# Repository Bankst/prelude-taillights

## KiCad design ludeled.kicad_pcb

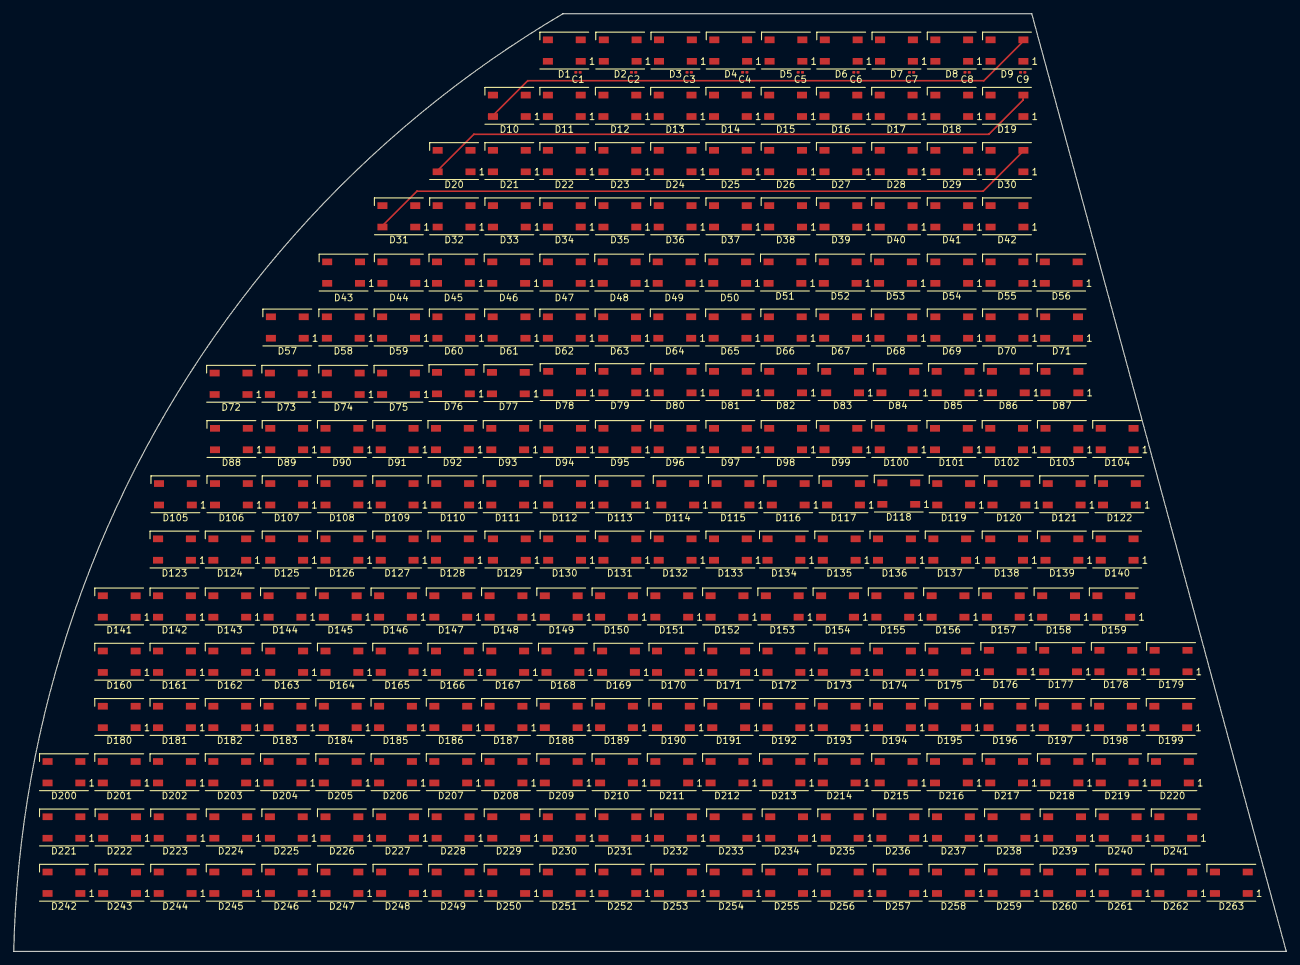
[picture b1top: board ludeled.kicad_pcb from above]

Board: 2 copper layers, 190.0 x 140.0 mm, 273 parts (1 on the bottom side), 224 nets.

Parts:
C1, C2, C3, C4, C5, C6, C7, C8, C9: 100nF; C_0201_0603Metric
D1, D2, D3, D4, D5, D6, D7, D8, D9, D10, D11, D12, D13, D14, D15, D16, D17, D18, D19, D20, D21, D22, D23, D24, D25, D26, D27, D28, D29, D30, D31, D32, D33, D34, D35, D36, D37, D38, D39, D40, D41, D42, D43, D44, D45, D46, D47, D48, D49, D50, D51, D52, D53, D54, D55, D56, D57, D58, D59, D60, D61, D62, D63, D64, D65, D66, D67, D68, D69, D70, D71, D72, D73, D74, D75, D76, D77, D78, D79, D80, D81, D82, D83, D84, D85, D86, D87, D88, D89, D90, D91, D92, D93, D94, D95, D96, D97, D98, D99, D100, D101, D102, D103, D104, D105, D106, D107, D108, D109, D110, D111, D112, D113, D114, D115, D116, D117, D118, D119, D120, D121, D122, D123, D124, D125, D126, D127, D128, D129, D130, D131, D132, D133, D134, D135, D136, D137, D138, D139, D140, D141, D142, D143, D144, D145, D146, D147, D148, D149, D150, D151, D152, D153, D154, D155, D156, D157, D158, D159, D160, D161, D162, D163, D164, D165, D166, D167, D168, D169, D170, D171, D172, D173, D174, D175, D176, D177, D178, D179, D180, D181, D182, D183, D184, D185, D186, D187, D188, D189, D190, D191, D192, D193, D194, D195, D196, D197, D198, D199, D200, D201, D202, D203, D204, D205, D206, D207, D208, D209, D210, D211, D212, D213, D214, D215, D216, D217, D218, D219, D220, D221, D222, D223, D224, D225, D226, D227, D228, D229, D230, D231, D232, D233, D234, D235, D236, D237, D238, D239, D240, D241, D242, D243, D244, D245, D246, D247, D248, D249, D250, D251, D252, D253, D254, D255, D256, D257, D258, D259, D260, D261, D262, D263: WS2812B; LED_WS2812B_PLCC4_5.0x5.0mm_P3.2mm
U1: ESP32-WROOM-32E

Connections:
+5V: C1.1, C2.1, C3.1, C4.1, C5.1, C6.1, C7.1, C8.1, C9.1, D1.1 (VDD), D2.1 (VDD), D3.1 (VDD), D4.1 (VDD), D5.1 (VDD), D6.1 (VDD), D7.1 (VDD), D8.1 (VDD), D9.1 (VDD), D10.1 (VDD), D11.1 (VDD), D12.1 (VDD), D13.1 (VDD), D14.1 (VDD), D15.1 (VDD), D16.1 (VDD), D17.1 (VDD), D18.1 (VDD), D19.1 (VDD), D20.1 (VDD), D21.1 (VDD), D22.1 (VDD), D23.1 (VDD), D24.1 (VDD), D25.1 (VDD), D26.1 (VDD), D27.1 (VDD), D28.1 (VDD), D29.1 (VDD), D30.1 (VDD), D31.1 (VDD), D32.1 (VDD), D33.1 (VDD), D34.1 (VDD), D35.1 (VDD), D36.1 (VDD), D37.1 (VDD), D38.1 (VDD), D39.1 (VDD), D40.1 (VDD), D41.1 (VDD), D42.1 (VDD), D43.1 (VDD), D44.1 (VDD), D45.1 (VDD), D46.1 (VDD), D47.1 (VDD), D48.1 (VDD), D49.1 (VDD), D50.1 (VDD), D51.1 (VDD), D52.1 (VDD), D53.1 (VDD), D54.1 (VDD), D55.1 (VDD), D56.1 (VDD), D57.1 (VDD), D58.1 (VDD), D59.1 (VDD), D60.1 (VDD), D61.1 (VDD), D62.1 (VDD), D63.1 (VDD), D64.1 (VDD), D65.1 (VDD), D66.1 (VDD), D67.1 (VDD), D68.1 (VDD), D69.1 (VDD), D70.1 (VDD), D71.1 (VDD), D72.1 (VDD), D73.1 (VDD), D74.1 (VDD), D75.1 (VDD), D76.1 (VDD), D77.1 (VDD), D78.1 (VDD), D79.1 (VDD), D80.1 (VDD), D81.1 (VDD), D82.1 (VDD), D83.1 (VDD), D84.1 (VDD), D85.1 (VDD), D86.1 (VDD), D87.1 (VDD), D88.1 (VDD), D89.1 (VDD), D90.1 (VDD), D91.1 (VDD), D92.1 (VDD), D93.1 (VDD), D94.1 (VDD), D95.1 (VDD), D96.1 (VDD), D97.1 (VDD), D98.1 (VDD), D99.1 (VDD), D100.1 (VDD), D101.1 (VDD), D102.1 (VDD), D103.1 (VDD), D104.1 (VDD), D105.1 (VDD), D106.1 (VDD), D107.1 (VDD), D108.1 (VDD), D109.1 (VDD), D110.1 (VDD), D111.1 (VDD), D112.1 (VDD), D113.1 (VDD), D114.1 (VDD), D115.1 (VDD), D116.1 (VDD), D117.1 (VDD), D118.1 (VDD), D119.1 (VDD), D120.1 (VDD), D121.1 (VDD), D122.1 (VDD), D123.1 (VDD), D124.1 (VDD), D125.1 (VDD), D126.1 (VDD), D127.1 (VDD), D128.1 (VDD), D129.1 (VDD), D130.1 (VDD), D131.1 (VDD), D132.1 (VDD), D133.1 (VDD), D134.1 (VDD), D135.1 (VDD), D136.1 (VDD), D137.1 (VDD), D138.1 (VDD), D139.1 (VDD), D140.1 (VDD), D141.1 (VDD), D142.1 (VDD), D143.1 (VDD), D144.1 (VDD), D145.1 (VDD), D146.1 (VDD), D147.1 (VDD), D148.1 (VDD), D149.1 (VDD), D150.1 (VDD), D151.1 (VDD), D152.1 (VDD), D153.1 (VDD), D154.1 (VDD), D155.1 (VDD), D156.1 (VDD), D157.1 (VDD), D158.1 (VDD), D159.1 (VDD), D160.1 (VDD), D161.1 (VDD), D162.1 (VDD), D163.1 (VDD), D164.1 (VDD), D165.1 (VDD), D166.1 (VDD), D167.1 (VDD), D168.1 (VDD), D169.1 (VDD), D170.1 (VDD), D171.1 (VDD), D172.1 (VDD), D173.1 (VDD), D174.1 (VDD), D175.1 (VDD), D176.1 (VDD), D177.1 (VDD), D178.1 (VDD), D179.1 (VDD), D180.1 (VDD), D181.1 (VDD), D182.1 (VDD), D183.1 (VDD), D184.1 (VDD), D185.1 (VDD), D186.1 (VDD), D187.1 (VDD), D188.1 (VDD), D189.1 (VDD), D190.1 (VDD), D191.1 (VDD), D192.1 (VDD), D193.1 (VDD), D194.1 (VDD), D195.1 (VDD), D196.1 (VDD), D197.1 (VDD), D198.1 (VDD), D199.1 (VDD), D200.1 (VDD), D201.1 (VDD), D202.1 (VDD), D203.1 (VDD), D204.1 (VDD), D205.1 (VDD), D206.1 (VDD), D207.1 (VDD), D208.1 (VDD), D209.1 (VDD), D210.1 (VDD), D211.1 (VDD), D212.1 (VDD), D213.1 (VDD), D214.1 (VDD), D215.1 (VDD), D216.1 (VDD), D217.1 (VDD), D218.1 (VDD), D219.1 (VDD), D220.1 (VDD), D221.1 (VDD), D222.1 (VDD), D223.1 (VDD), D224.1 (VDD), D225.1 (VDD), D226.1 (VDD), D227.1 (VDD), D228.1 (VDD), D229.1 (VDD), D230.1 (VDD), D231.1 (VDD), D232.1 (VDD), D233.1 (VDD), D234.1 (VDD), D235.1 (VDD), D236.1 (VDD), D237.1 (VDD), D238.1 (VDD), D239.1 (VDD), D240.1 (VDD), D241.1 (VDD), D242.1 (VDD), D243.1 (VDD), D244.1 (VDD), D245.1 (VDD), D246.1 (VDD), D247.1 (VDD), D248.1 (VDD), D249.1 (VDD), D250.1 (VDD), D251.1 (VDD), D252.1 (VDD), D253.1 (VDD), D254.1 (VDD), D255.1 (VDD), D256.1 (VDD), D257.1 (VDD), D258.1 (VDD), D259.1 (VDD), D260.1 (VDD), D261.1 (VDD), D262.1 (VDD), D263.1 (VDD)
/FrontLeds/LED_LOWER_DIN: D1.4 (DIN), U1.29
GND: C1.2, C2.2, C3.2, C4.2, C5.2, C6.2, C7.2, C8.2, C9.2, D1.3 (VSS), D2.3 (VSS), D3.3 (VSS), D4.3 (VSS), D5.3 (VSS), D6.3 (VSS), D7.3 (VSS), D8.3 (VSS), D9.3 (VSS), D10.3 (VSS), D11.3 (VSS), D12.3 (VSS), D13.3 (VSS), D14.3 (VSS), D15.3 (VSS), D16.3 (VSS), D17.3 (VSS), D18.3 (VSS), D19.3 (VSS), D20.3 (VSS), D21.3 (VSS), D22.3 (VSS), D23.3 (VSS), D24.3 (VSS), D25.3 (VSS), D26.3 (VSS), D27.3 (VSS), D28.3 (VSS), D29.3 (VSS), D30.3 (VSS), D31.3 (VSS), D32.3 (VSS), D33.3 (VSS), D34.3 (VSS), D35.3 (VSS), D36.3 (VSS), D37.3 (VSS), D38.3 (VSS), D39.3 (VSS), D40.3 (VSS), D41.3 (VSS), D42.3 (VSS), D43.3 (VSS), D44.3 (VSS), D45.3 (VSS), D46.3 (VSS), D47.3 (VSS), D48.3 (VSS), D49.3 (VSS), D50.3 (VSS), D51.3 (VSS), D52.3 (VSS), D53.3 (VSS), D54.3 (VSS), D55.3 (VSS), D56.3 (VSS), D57.3 (VSS), D58.3 (VSS), D59.3 (VSS), D60.3 (VSS), D61.3 (VSS), D62.3 (VSS), D63.3 (VSS), D64.3 (VSS), D65.3 (VSS), D66.3 (VSS), D67.3 (VSS), D68.3 (VSS), D69.3 (VSS), D70.3 (VSS), D71.3 (VSS), D72.3 (VSS), D73.3 (VSS), D74.3 (VSS), D75.3 (VSS), D76.3 (VSS), D77.3 (VSS), D78.3 (VSS), D79.3 (VSS), D80.3 (VSS), D81.3 (VSS), D82.3 (VSS), D83.3 (VSS), D84.3 (VSS), D85.3 (VSS), D86.3 (VSS), D87.3 (VSS), D88.3 (VSS), D89.3 (VSS), D90.3 (VSS), D91.3 (VSS), D92.3 (VSS), D93.3 (VSS), D94.3 (VSS), D95.3 (VSS), D96.3 (VSS), D97.3 (VSS), D98.3 (VSS), D99.3 (VSS), D100.3 (VSS), D101.3 (VSS), D102.3 (VSS), D103.3 (VSS), D104.3 (VSS), D105.3 (VSS), D106.3 (VSS), D107.3 (VSS), D108.3 (VSS), D109.3 (VSS), D110.3 (VSS), D111.3 (VSS), D112.3 (VSS), D113.3 (VSS), D114.3 (VSS), D115.3 (VSS), D116.3 (VSS), D117.3 (VSS), D118.3 (VSS), D119.3 (VSS), D120.3 (VSS), D121.3 (VSS), D122.3 (VSS), D123.3 (VSS), D124.3 (VSS), D125.3 (VSS), D126.3 (VSS), D127.3 (VSS), D128.3 (VSS), D129.3 (VSS), D130.3 (VSS), D131.3 (VSS), D132.3 (VSS), D133.3 (VSS), D134.3 (VSS), D135.3 (VSS), D136.3 (VSS), D137.3 (VSS), D138.3 (VSS), D139.3 (VSS), D140.3 (VSS), D141.3 (VSS), D142.3 (VSS), D143.3 (VSS), D144.3 (VSS), D145.3 (VSS), D146.3 (VSS), D147.3 (VSS), D148.3 (VSS), D149.3 (VSS), D150.3 (VSS), D151.3 (VSS), D152.3 (VSS), D153.3 (VSS), D154.3 (VSS), D155.3 (VSS), D156.3 (VSS), D157.3 (VSS), D158.3 (VSS), D159.3 (VSS), D160.3 (VSS), D161.3 (VSS), D162.3 (VSS), D163.3 (VSS), D164.3 (VSS), D165.3 (VSS), D166.3 (VSS), D167.3 (VSS), D168.3 (VSS), D169.3 (VSS), D170.3 (VSS), D171.3 (VSS), D172.3 (VSS), D173.3 (VSS), D174.3 (VSS), D175.3 (VSS), D176.3 (VSS), D177.3 (VSS), D178.3 (VSS), D179.3 (VSS), D180.3 (VSS), D181.3 (VSS), D182.3 (VSS), D183.3 (VSS), D184.3 (VSS), D185.3 (VSS), D186.3 (VSS), D187.3 (VSS), D188.3 (VSS), D189.3 (VSS), D190.3 (VSS), D191.3 (VSS), D192.3 (VSS), D193.3 (VSS), D194.3 (VSS), D195.3 (VSS), D196.3 (VSS), D197.3 (VSS), D198.3 (VSS), D199.3 (VSS), D200.3 (VSS), D201.3 (VSS), D202.3 (VSS), D203.3 (VSS), D204.3 (VSS), D205.3 (VSS), D206.3 (VSS), D207.3 (VSS), D208.3 (VSS), D209.3 (VSS), D210.3 (VSS), D211.3 (VSS), D212.3 (VSS), D213.3 (VSS), D214.3 (VSS), D215.3 (VSS), D216.3 (VSS), D217.3 (VSS), D218.3 (VSS), D219.3 (VSS), D220.3 (VSS), D221.3 (VSS), D222.3 (VSS), D223.3 (VSS), D224.3 (VSS), D225.3 (VSS), D226.3 (VSS), D227.3 (VSS), D228.3 (VSS), D229.3 (VSS), D230.3 (VSS), D231.3 (VSS), D232.3 (VSS), D233.3 (VSS), D234.3 (VSS), D235.3 (VSS), D236.3 (VSS), D237.3 (VSS), D238.3 (VSS), D239.3 (VSS), D240.3 (VSS), D241.3 (VSS), D242.3 (VSS), D243.3 (VSS), D244.3 (VSS), D245.3 (VSS), D246.3 (VSS), D247.3 (VSS), D248.3 (VSS), D249.3 (VSS), D250.3 (VSS), D251.3 (VSS), D252.3 (VSS), D253.3 (VSS), D254.3 (VSS), D255.3 (VSS), D256.3 (VSS), D257.3 (VSS), D258.3 (VSS), D259.3 (VSS), D260.3 (VSS), D261.3 (VSS), D262.3 (VSS), D263.3 (VSS), U1.1, U1.15, U1.38
unnamed: D1.2 (DOUT), D2.4 (DIN)
unnamed: D2.2 (DOUT), D3.4 (DIN)
unnamed: D3.2 (DOUT), D4.4 (DIN)
unnamed: D4.2 (DOUT), D5.4 (DIN)
unnamed: D5.2 (DOUT), D6.4 (DIN)
unnamed: D6.2 (DOUT), D7.4 (DIN)
unnamed: D7.2 (DOUT), D8.4 (DIN)
unnamed: D8.2 (DOUT), D9.4 (DIN)
unnamed: D10.2 (DOUT), D11.4 (DIN)
unnamed: D9.2 (DOUT), D10.4 (DIN)
unnamed: D11.2 (DOUT), D12.4 (DIN)
unnamed: D12.2 (DOUT), D13.4 (DIN)
unnamed: D13.2 (DOUT), D14.4 (DIN)
unnamed: D14.2 (DOUT), D15.4 (DIN)
unnamed: D15.2 (DOUT), D16.4 (DIN)
unnamed: D16.2 (DOUT), D17.4 (DIN)
unnamed: D17.2 (DOUT), D18.4 (DIN)
unnamed: D18.2 (DOUT), D19.4 (DIN)
unnamed: D19.2 (DOUT), D20.4 (DIN)
unnamed: D20.2 (DOUT), D21.4 (DIN)
unnamed: D21.2 (DOUT), D22.4 (DIN)
unnamed: D22.2 (DOUT), D23.4 (DIN)
unnamed: D23.2 (DOUT), D24.4 (DIN)
unnamed: D24.2 (DOUT), D25.4 (DIN)
unnamed: D25.2 (DOUT), D26.4 (DIN)
unnamed: D26.2 (DOUT), D27.4 (DIN)
unnamed: D27.2 (DOUT), D28.4 (DIN)
unnamed: D28.2 (DOUT), D29.4 (DIN)
unnamed: D29.2 (DOUT), D30.4 (DIN)
unnamed: D30.2 (DOUT), D31.4 (DIN)
unnamed: D31.2 (DOUT), D32.4 (DIN)
unnamed: D32.2 (DOUT), D33.4 (DIN)
unnamed: D33.2 (DOUT), D34.4 (DIN)
unnamed: D34.2 (DOUT), D35.4 (DIN)
unnamed: D35.2 (DOUT), D36.4 (DIN)
unnamed: D36.2 (DOUT), D37.4 (DIN)
unnamed: D37.2 (DOUT), D38.4 (DIN)
unnamed: D38.2 (DOUT), D39.4 (DIN)
unnamed: D39.2 (DOUT), D40.4 (DIN)
unnamed: D40.2 (DOUT), D41.4 (DIN)
unnamed: D41.2 (DOUT), D42.4 (DIN)
unnamed: D42.2 (DOUT), D43.4 (DIN)
unnamed: D43.2 (DOUT), D44.4 (DIN)
unnamed: D44.2 (DOUT), D45.4 (DIN)
unnamed: D45.2 (DOUT), D46.4 (DIN)
unnamed: D46.2 (DOUT), D47.4 (DIN)
unnamed: D47.2 (DOUT), D48.4 (DIN)
unnamed: D48.2 (DOUT), D49.4 (DIN)
unnamed: D49.2 (DOUT), D50.4 (DIN)
unnamed: D50.2 (DOUT), D51.4 (DIN)
unnamed: D51.2 (DOUT), D52.4 (DIN)
unnamed: D52.2 (DOUT), D53.4 (DIN)
unnamed: D53.2 (DOUT), D54.4 (DIN)
unnamed: D54.2 (DOUT), D55.4 (DIN)
unnamed: D55.2 (DOUT), D56.4 (DIN)
unnamed: D56.2 (DOUT), D57.4 (DIN)
unnamed: D57.2 (DOUT), D58.4 (DIN)
unnamed: D58.2 (DOUT), D59.4 (DIN)
unnamed: D59.2 (DOUT), D60.4 (DIN)
unnamed: D60.2 (DOUT), D61.4 (DIN)
unnamed: D61.2 (DOUT), D62.4 (DIN)
unnamed: D62.2 (DOUT), D63.4 (DIN)
unnamed: D63.2 (DOUT), D64.4 (DIN)
unnamed: D64.2 (DOUT), D65.4 (DIN)
unnamed: D65.2 (DOUT), D66.4 (DIN)
unnamed: D66.2 (DOUT), D67.4 (DIN)
unnamed: D67.2 (DOUT), D68.4 (DIN)
unnamed: D68.2 (DOUT), D69.4 (DIN)
unnamed: D69.2 (DOUT), D70.4 (DIN)
unnamed: D70.2 (DOUT), D71.4 (DIN)
unnamed: D71.2 (DOUT), D72.4 (DIN)
unnamed: D72.2 (DOUT), D73.4 (DIN)
unnamed: D73.2 (DOUT), D74.4 (DIN)
unnamed: D74.2 (DOUT), D75.4 (DIN)
unnamed: D75.2 (DOUT), D76.4 (DIN)
unnamed: D76.2 (DOUT), D77.4 (DIN)
unnamed: D77.2 (DOUT), D78.4 (DIN)
unnamed: D78.2 (DOUT), D79.4 (DIN)
unnamed: D79.2 (DOUT), D80.4 (DIN)
unnamed: D80.2 (DOUT), D81.4 (DIN)
unnamed: D81.2 (DOUT), D82.4 (DIN)
unnamed: D82.2 (DOUT), D83.4 (DIN)
unnamed: D83.2 (DOUT), D84.4 (DIN)
unnamed: D84.2 (DOUT), D85.4 (DIN)
unnamed: D85.2 (DOUT), D86.4 (DIN)
unnamed: D86.2 (DOUT), D87.4 (DIN)
unnamed: D87.2 (DOUT), D88.4 (DIN)
unnamed: D88.2 (DOUT), D89.4 (DIN)
unnamed: D89.2 (DOUT), D90.4 (DIN)
unnamed: D90.2 (DOUT), D91.4 (DIN)
unnamed: D91.2 (DOUT), D92.4 (DIN)
unnamed: D92.2 (DOUT), D93.4 (DIN)
unnamed: D93.2 (DOUT), D94.4 (DIN)
unnamed: D94.2 (DOUT), D95.4 (DIN)
unnamed: D95.2 (DOUT), D96.4 (DIN)
unnamed: D96.2 (DOUT), D97.4 (DIN)
unnamed: D97.2 (DOUT), D98.4 (DIN)
unnamed: D98.2 (DOUT), D99.4 (DIN)
unnamed: D100.2 (DOUT), D101.4 (DIN)
unnamed: D99.2 (DOUT), D100.4 (DIN)
unnamed: D101.2 (DOUT), D102.4 (DIN)
unnamed: D102.2 (DOUT), D103.4 (DIN)
unnamed: D103.2 (DOUT), D104.4 (DIN)
unnamed: D104.2 (DOUT), D105.4 (DIN)
unnamed: D105.2 (DOUT), D106.4 (DIN)
unnamed: D106.2 (DOUT), D107.4 (DIN)
unnamed: D107.2 (DOUT), D108.4 (DIN)
unnamed: D108.2 (DOUT), D109.4 (DIN)
unnamed: D109.2 (DOUT), D110.4 (DIN)
unnamed: D110.2 (DOUT), D111.4 (DIN)
unnamed: D111.2 (DOUT), D112.4 (DIN)
unnamed: D112.2 (DOUT), D113.4 (DIN)
unnamed: D113.2 (DOUT), D114.4 (DIN)
unnamed: D114.2 (DOUT), D115.4 (DIN)
unnamed: D115.2 (DOUT), D116.4 (DIN)
unnamed: D116.2 (DOUT), D117.4 (DIN)
unnamed: D117.2 (DOUT), D118.4 (DIN)
unnamed: D118.2 (DOUT), D119.4 (DIN)
unnamed: D119.2 (DOUT), D120.4 (DIN)
unnamed: D120.2 (DOUT), D121.4 (DIN)
unnamed: D121.2 (DOUT), D122.4 (DIN)
unnamed: D122.2 (DOUT), D123.4 (DIN)
unnamed: D123.2 (DOUT), D124.4 (DIN)
unnamed: D124.2 (DOUT), D125.4 (DIN)
unnamed: D125.2 (DOUT), D126.4 (DIN)
unnamed: D126.2 (DOUT), D127.4 (DIN)
unnamed: D127.2 (DOUT), D128.4 (DIN)
unnamed: D128.2 (DOUT), D129.4 (DIN)
unnamed: D129.2 (DOUT), D130.4 (DIN)
unnamed: D130.2 (DOUT), D131.4 (DIN)
unnamed: D131.2 (DOUT), D132.4 (DIN)
unnamed: D132.2 (DOUT), D133.4 (DIN)
unnamed: D133.2 (DOUT), D134.4 (DIN)
unnamed: D134.2 (DOUT), D135.4 (DIN)
unnamed: D135.2 (DOUT), D136.4 (DIN)
unnamed: D136.2 (DOUT), D137.4 (DIN)
unnamed: D137.2 (DOUT), D138.4 (DIN)
unnamed: D138.2 (DOUT), D139.4 (DIN)
unnamed: D139.2 (DOUT), D140.4 (DIN)
unnamed: D140.2 (DOUT), D141.4 (DIN)
unnamed: D141.2 (DOUT), D142.4 (DIN)
unnamed: D142.2 (DOUT), D143.4 (DIN)
unnamed: D143.2 (DOUT), D144.4 (DIN)
unnamed: D144.2 (DOUT), D145.4 (DIN)
unnamed: D145.2 (DOUT), D146.4 (DIN)
unnamed: D146.2 (DOUT), D147.4 (DIN)
unnamed: D147.2 (DOUT), D148.4 (DIN)
unnamed: D148.2 (DOUT), D149.4 (DIN)
unnamed: D149.2 (DOUT), D150.4 (DIN)
unnamed: D150.2 (DOUT), D151.4 (DIN)
unnamed: D151.2 (DOUT), D152.4 (DIN)
unnamed: D152.2 (DOUT), D153.4 (DIN)
unnamed: D153.2 (DOUT), D154.4 (DIN)
unnamed: D154.2 (DOUT), D155.4 (DIN)
unnamed: D155.2 (DOUT), D156.4 (DIN)
unnamed: D156.2 (DOUT), D157.4 (DIN)
unnamed: D157.2 (DOUT), D158.4 (DIN)
unnamed: D158.2 (DOUT), D159.4 (DIN)
unnamed: D159.2 (DOUT), D160.4 (DIN)
unnamed: D160.2 (DOUT), D161.4 (DIN)
unnamed: D161.2 (DOUT), D162.4 (DIN)
unnamed: D162.2 (DOUT), D163.4 (DIN)
unnamed: D163.2 (DOUT), D164.4 (DIN)
unnamed: D164.2 (DOUT), D165.4 (DIN)
unnamed: D165.2 (DOUT), D166.4 (DIN)
unnamed: D166.2 (DOUT), D167.4 (DIN)
unnamed: D167.2 (DOUT), D168.4 (DIN)
unnamed: D168.2 (DOUT), D169.4 (DIN)
unnamed: D169.2 (DOUT), D170.4 (DIN)
unnamed: D170.2 (DOUT), D171.4 (DIN)
unnamed: D171.2 (DOUT), D172.4 (DIN)
unnamed: D172.2 (DOUT), D173.4 (DIN)
unnamed: D173.2 (DOUT), D174.4 (DIN)
unnamed: D174.2 (DOUT), D175.4 (DIN)
unnamed: D175.2 (DOUT), D176.4 (DIN)
unnamed: D176.2 (DOUT), D177.4 (DIN)
unnamed: D177.2 (DOUT), D178.4 (DIN)
unnamed: D178.2 (DOUT), D179.4 (DIN)
unnamed: D179.2 (DOUT), D180.4 (DIN)
unnamed: D180.2 (DOUT), D181.4 (DIN)
unnamed: D181.2 (DOUT), D182.4 (DIN)
unnamed: D182.2 (DOUT), D183.4 (DIN)
unnamed: D183.2 (DOUT), D184.4 (DIN)
unnamed: D184.2 (DOUT), D185.4 (DIN)
unnamed: D185.2 (DOUT), D186.4 (DIN)
unnamed: D186.2 (DOUT), D187.4 (DIN)
unnamed: D187.2 (DOUT), D188.4 (DIN)
unnamed: D188.2 (DOUT), D189.4 (DIN)
unnamed: D190.2 (DOUT), D191.4 (DIN)
unnamed: D189.2 (DOUT), D190.4 (DIN)
unnamed: D191.2 (DOUT), D192.4 (DIN)
unnamed: D192.2 (DOUT), D193.4 (DIN)
unnamed: D193.2 (DOUT), D194.4 (DIN)
unnamed: D194.2 (DOUT), D195.4 (DIN)
unnamed: D195.2 (DOUT), D196.4 (DIN)
unnamed: D196.2 (DOUT), D197.4 (DIN)
unnamed: D197.2 (DOUT), D198.4 (DIN)
unnamed: D198.2 (DOUT), D199.4 (DIN)
unnamed: D199.2 (DOUT), D200.4 (DIN)
unnamed: D200.2 (DOUT), D201.4 (DIN)
unnamed: D201.2 (DOUT), D202.4 (DIN)
unnamed: D202.2 (DOUT), D203.4 (DIN)
unnamed: D203.2 (DOUT), D204.4 (DIN)
unnamed: D204.2 (DOUT), D205.4 (DIN)
unnamed: D205.2 (DOUT), D206.4 (DIN)
unnamed: D206.2 (DOUT), D207.4 (DIN)
unnamed: D207.2 (DOUT), D208.4 (DIN)
unnamed: D208.2 (DOUT), D209.4 (DIN)
unnamed: D209.2 (DOUT), D210.4 (DIN)
unnamed: D211.2 (DOUT), D212.4 (DIN)
unnamed: D210.2 (DOUT), D211.4 (DIN)
unnamed: D212.2 (DOUT), D213.4 (DIN)
unnamed: D213.2 (DOUT), D214.4 (DIN)
unnamed: D214.2 (DOUT), D215.4 (DIN)
unnamed: D215.2 (DOUT), D216.4 (DIN)
unnamed: D216.2 (DOUT), D217.4 (DIN)
unnamed: D217.2 (DOUT), D218.4 (DIN)
unnamed: D218.2 (DOUT), D219.4 (DIN)
unnamed: D219.2 (DOUT), D220.4 (DIN)
unnamed: D220.2 (DOUT), D221.4 (DIN), D222.4 (DIN), D223.4 (DIN), D224.4 (DIN), D225.4 (DIN), D226.4 (DIN), D227.4 (DIN), D228.4 (DIN), D229.4 (DIN), D230.4 (DIN), D231.4 (DIN), D232.4 (DIN), D233.4 (DIN), D234.4 (DIN), D235.4 (DIN), D236.4 (DIN), D237.4 (DIN), D238.4 (DIN), D239.4 (DIN), D240.4 (DIN), D241.4 (DIN), D242.4 (DIN), D243.4 (DIN), D244.4 (DIN), D245.4 (DIN), D246.4 (DIN), D247.4 (DIN), D248.4 (DIN), D249.4 (DIN), D250.4 (DIN), D251.4 (DIN), D252.4 (DIN), D253.4 (DIN), D254.4 (DIN), D255.4 (DIN), D256.4 (DIN), D257.4 (DIN), D258.4 (DIN), D259.4 (DIN), D260.4 (DIN), D261.4 (DIN), D262.4 (DIN), D263.4 (DIN)
unnamed: D221.2 (DOUT), D222.2 (DOUT), D223.2 (DOUT), D224.2 (DOUT), D225.2 (DOUT), D226.2 (DOUT), D227.2 (DOUT), D228.2 (DOUT), D229.2 (DOUT), D230.2 (DOUT), D231.2 (DOUT), D232.2 (DOUT), D233.2 (DOUT), D234.2 (DOUT), D235.2 (DOUT), D236.2 (DOUT), D237.2 (DOUT), D238.2 (DOUT), D239.2 (DOUT), D240.2 (DOUT), D241.2 (DOUT), D242.2 (DOUT), D243.2 (DOUT), D244.2 (DOUT), D245.2 (DOUT), D246.2 (DOUT), D247.2 (DOUT), D248.2 (DOUT), D249.2 (DOUT), D250.2 (DOUT), D251.2 (DOUT), D252.2 (DOUT), D253.2 (DOUT), D254.2 (DOUT), D255.2 (DOUT), D256.2 (DOUT), D257.2 (DOUT), D258.2 (DOUT), D259.2 (DOUT), D260.2 (DOUT), D261.2 (DOUT), D262.2 (DOUT), D263.2 (DOUT)

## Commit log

2022-09-14 Kicad6 Update, add ws2812 3d
2022-09-15 More layout
2022-09-15 layout done
2022-10-17 Major layout and placement complete
2022-10-31 DRC fixes, cap footprint update, etc.
2022-11-03 Rename, remove ESP32, update gitignores
2022-11-03 Project re-arrange, begin controller
2023-07-19 tail pico code
